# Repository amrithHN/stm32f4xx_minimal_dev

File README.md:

# Stm32f407 based board with barometer sensor

GPL license

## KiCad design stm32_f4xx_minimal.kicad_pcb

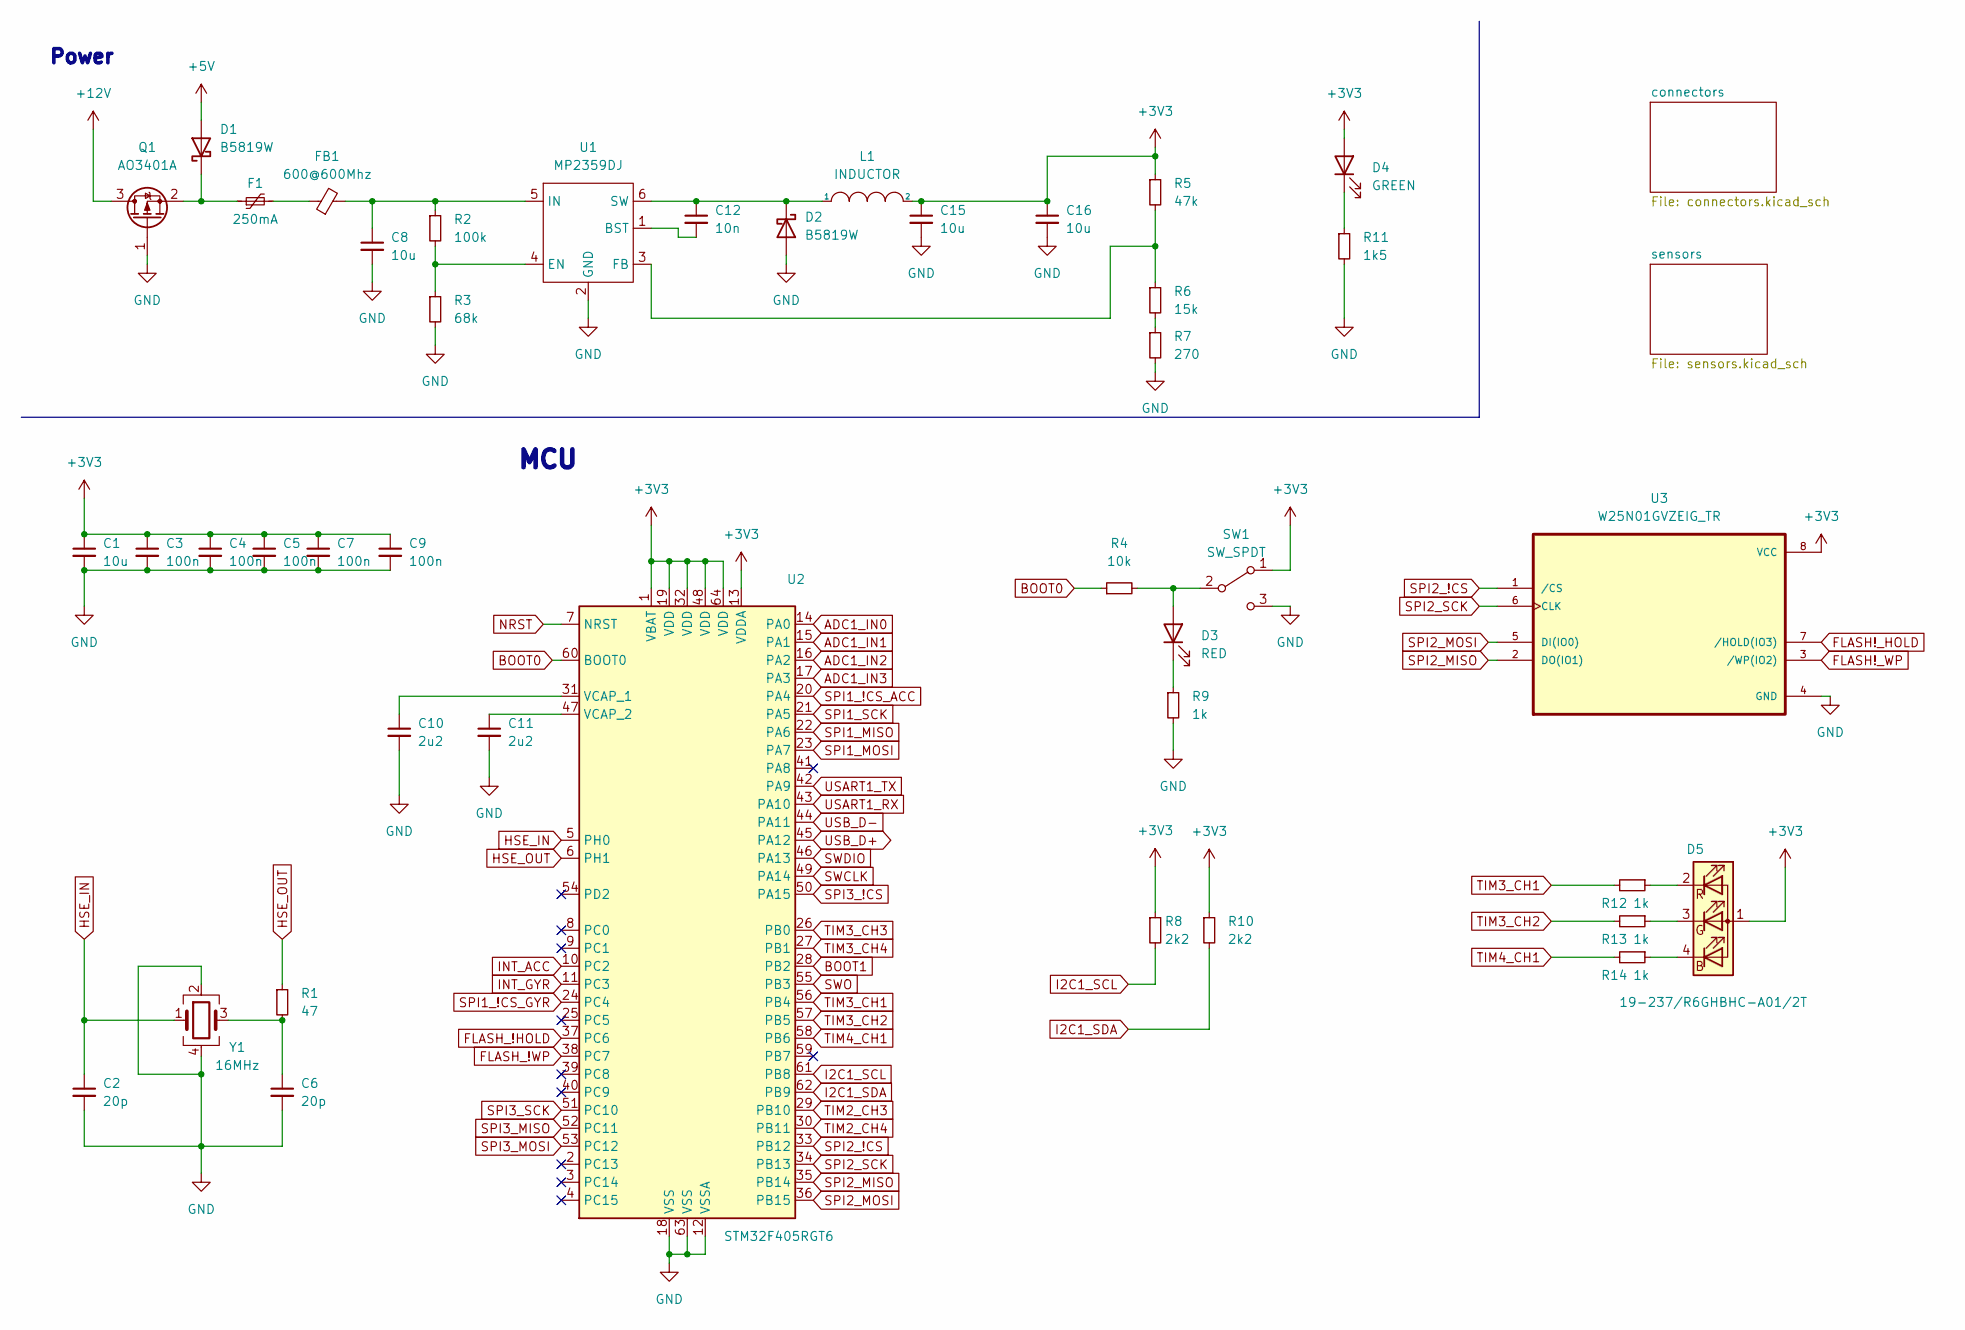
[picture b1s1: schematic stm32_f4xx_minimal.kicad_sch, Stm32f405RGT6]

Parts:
C1, C8: 10u; C_1206_3216Metric
C2, C6: 20p; C_0402_1005Metric
C3, C4, C5, C7, C9: 100n; C_0402_1005Metric
C10, C11: 2u2; C_0603_1608Metric
C12: 10n; C_0402_1005Metric
C15, C16: 10u; C_0603_1608Metric
D1, D2: B5819W; SOD3716X135N
D3: RED; LED_0603_1608Metric
D4: GREEN; LED_0603_1608Metric
D5: 19-237/R6GHBHC-A01/2T; 19-237-R6GHBHC-A01-2T
F1: 250mA; Fuse_1206_3216Metric
FB1: 600@600Mhz; L_0805_2012Metric
L1: INDUCTOR; L_Sunlord_MWSA0518_5.4x5.2mm
Q1: AO3401A; SOT-23
R1: 47; R_0402_1005Metric
R2: 100k; R_0603_1608Metric
R3: 68k; R_0603_1608Metric
R4: 10k; R_0603_1608Metric
R5: 47k; R_0603_1608Metric
R6: 15k; R_0603_1608Metric
R7: 270; R_0603_1608Metric
R8, R10: 2k2; R_0603_1608Metric
R9, R12, R13, R14: 1k; R_0603_1608Metric
R11: 1k5; R_0603_1608Metric
SW1: SW_SPDT; SW_SPDT_PCM12
U1: MP2359DJ; SOT-23-6
U2: STM32F405RGT6; LQFP-64_10x10mm_P0.5mm
U3: W25N01GVZEIG_TR; W25N01GVZEIG
Y1: 16MHz; Crystal_SMD_3225-4Pin_3.2x2.5mm

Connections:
+3V3: C1.1, C3.1, C4.1, C5.1, C7.1, C9.1, C15.1, C16.1, D4.2 (A), D5.1 (A), L1.2, R5.1, R8.1, R10.1, SW1.1 (A), U2.1 (VBAT), U2.13 (VDDA), U2.19 (VDD), U2.32 (VDD), U2.48 (VDD), U2.64 (VDD), U3.8 (VCC); also elsewhere on the board
+5V: D1.2 (A); also elsewhere on the board
+12V: Q1.3 (D); also elsewhere on the board
ADC1_IN0: U2.14 (PA0); also elsewhere on the board
ADC1_IN1: U2.15 (PA1); also elsewhere on the board
ADC1_IN2: U2.16 (PA2); also elsewhere on the board
ADC1_IN3: U2.17 (PA3); also elsewhere on the board
BOOT0: R4.1, U2.60 (BOOT0)
BOOT1: U2.28 (PB2)
FLASH!_HOLD: U3.7 (/HOLD(IO3))
FLASH!_WP: U3.3 (/WP(IO2))
FLASH_!HOLD: U2.37 (PC6)
FLASH_!WP: U2.38 (PC7)
GND: C1.2, C2.2, C3.2, C4.2, C5.2, C6.2, C7.2, C8.2, C9.2, C10.2, C11.2, C15.2, C16.2, D2.2 (A), Q1.1 (G), R3.2, R7.2, R9.2, R11.2, SW1.3 (C), U1.2 (GND), U2.12 (VSSA), U2.18 (VSS), U2.63 (VSS), U3.4 (GND), Y1.2, Y1.4; also elsewhere on the board
HSE_IN: C2.1, U2.5 (PH0), Y1.1
HSE_OUT: R1.1, U2.6 (PH1)
I2C1_SCL: R8.2, U2.61 (PB8); also elsewhere on the board
I2C1_SDA: R10.2, U2.62 (PB9); also elsewhere on the board
INT_ACC: U2.10 (PC2); also elsewhere on the board
INT_GYR: U2.11 (PC3); also elsewhere on the board
NRST: U2.7 (NRST); also elsewhere on the board
unnamed: C6.1, R1.2, Y1.3
unnamed: C8.1, FB1.2, R2.1, U1.5 (IN)
unnamed: C10.1, U2.31 (VCAP_1)
unnamed: C11.1, U2.47 (VCAP_2)
unnamed: C12.1, D2.1 (K), L1.1, U1.6 (SW)
unnamed: C12.2, U1.1 (BST)
unnamed: D1.1 (K), F1.1, Q1.2 (S)
unnamed: D3.1 (K), R9.1
unnamed: D3.2 (A), R4.2, SW1.2 (B)
unnamed: D4.1 (K), R11.1
unnamed: D5.2 (RK), R12.1
unnamed: D5.3 (GK), R13.1
unnamed: D5.4 (BK), R14.1
unnamed: F1.2, FB1.1
unnamed: R2.2, R3.1, U1.4 (EN)
unnamed: R5.2, R6.1, U1.3 (FB)
unnamed: R6.2, R7.1
SPI1_!CS_ACC: U2.20 (PA4); also elsewhere on the board
SPI1_!CS_GYR: U2.24 (PC4); also elsewhere on the board
SPI1_MISO: U2.22 (PA6); also elsewhere on the board
SPI1_MOSI: U2.23 (PA7); also elsewhere on the board
SPI1_SCK: U2.21 (PA5); also elsewhere on the board
SPI2_!CS: U2.33 (PB12), U3.1 (/CS)
SPI2_MISO: U2.35 (PB14), U3.2 (DO(IO1))
SPI2_MOSI: U2.36 (PB15), U3.5 (DI(IO0))
SPI2_SCK: U2.34 (PB13), U3.6 (CLK)
SPI3_!CS: U2.50 (PA15); also elsewhere on the board
SPI3_MISO: U2.52 (PC11); also elsewhere on the board
SPI3_MOSI: U2.53 (PC12); also elsewhere on the board
SPI3_SCK: U2.51 (PC10); also elsewhere on the board
SWCLK: U2.49 (PA14); also elsewhere on the board
SWDIO: U2.46 (PA13); also elsewhere on the board
SWO: U2.55 (PB3); also elsewhere on the board
TIM2_CH3: U2.29 (PB10); also elsewhere on the board
TIM2_CH4: U2.30 (PB11); also elsewhere on the board
TIM3_CH1: R12.2, U2.56 (PB4)
TIM3_CH2: R13.2, U2.57 (PB5)
TIM3_CH3: U2.26 (PB0); also elsewhere on the board
TIM3_CH4: U2.27 (PB1); also elsewhere on the board
TIM4_CH1: R14.2, U2.58 (PB6)
USART1_RX: U2.43 (PA10); also elsewhere on the board
USART1_TX: U2.42 (PA9); also elsewhere on the board
USB_D+: U2.45 (PA12); also elsewhere on the board
USB_D-: U2.44 (PA11); also elsewhere on the board

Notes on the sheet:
MCU
Power

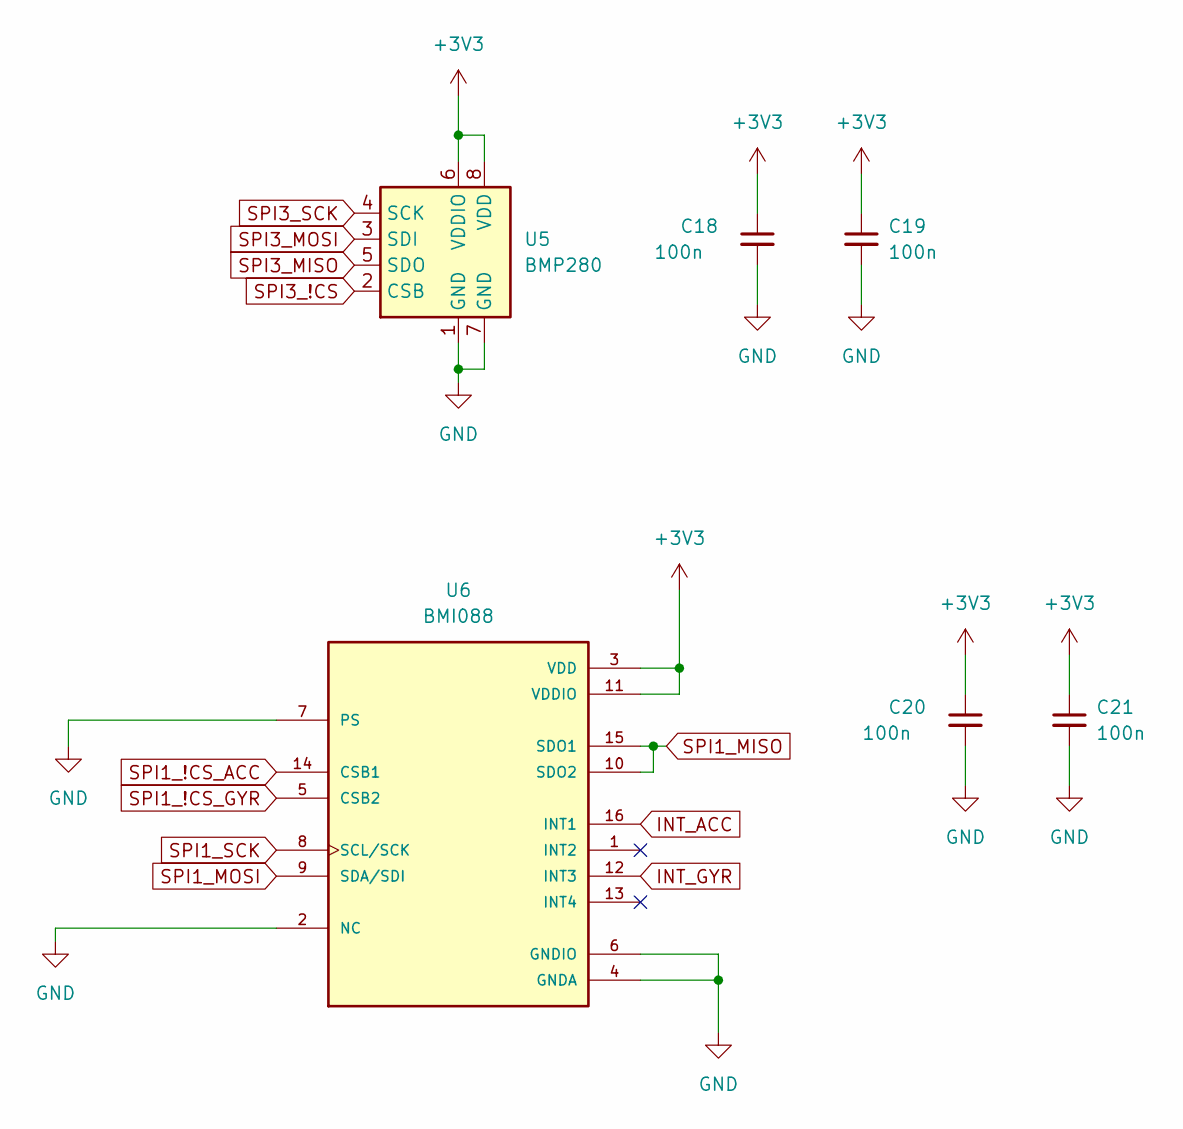
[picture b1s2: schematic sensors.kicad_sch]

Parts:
C18, C19, C20, C21: 100n; C_0402_1005Metric
U5: BMP280; Bosch_LGA-8_2x2.5mm_P0.65mm_ClockwisePinNumbering
U6: BMI088

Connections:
+3V3: C18.1, C19.1, C20.1, C21.1, U5.6 (VDDIO), U5.8 (VDD), U6.3 (VDD), U6.11 (VDDIO); also elsewhere on the board
GND: C18.2, C19.2, C20.2, C21.2, U5.1 (GND), U5.7 (GND), U6.2 (NC), U6.4 (GNDA), U6.6 (GNDIO), U6.7 (PS); also elsewhere on the board
INT_ACC: U6.16 (INT1); also elsewhere on the board
INT_GYR: U6.12 (INT3); also elsewhere on the board
SPI1_!CS_ACC: U6.14 (CSB1); also elsewhere on the board
SPI1_!CS_GYR: U6.5 (CSB2); also elsewhere on the board
SPI1_MISO: U6.10 (SDO2), U6.15 (SDO1); also elsewhere on the board
SPI1_MOSI: U6.9 (SDA/SDI); also elsewhere on the board
SPI1_SCK: U6.8 (SCL/SCK); also elsewhere on the board
SPI3_!CS: U5.2 (CSB); also elsewhere on the board
SPI3_MISO: U5.5 (SDO); also elsewhere on the board
SPI3_MOSI: U5.3 (SDI); also elsewhere on the board
SPI3_SCK: U5.4 (SCK); also elsewhere on the board

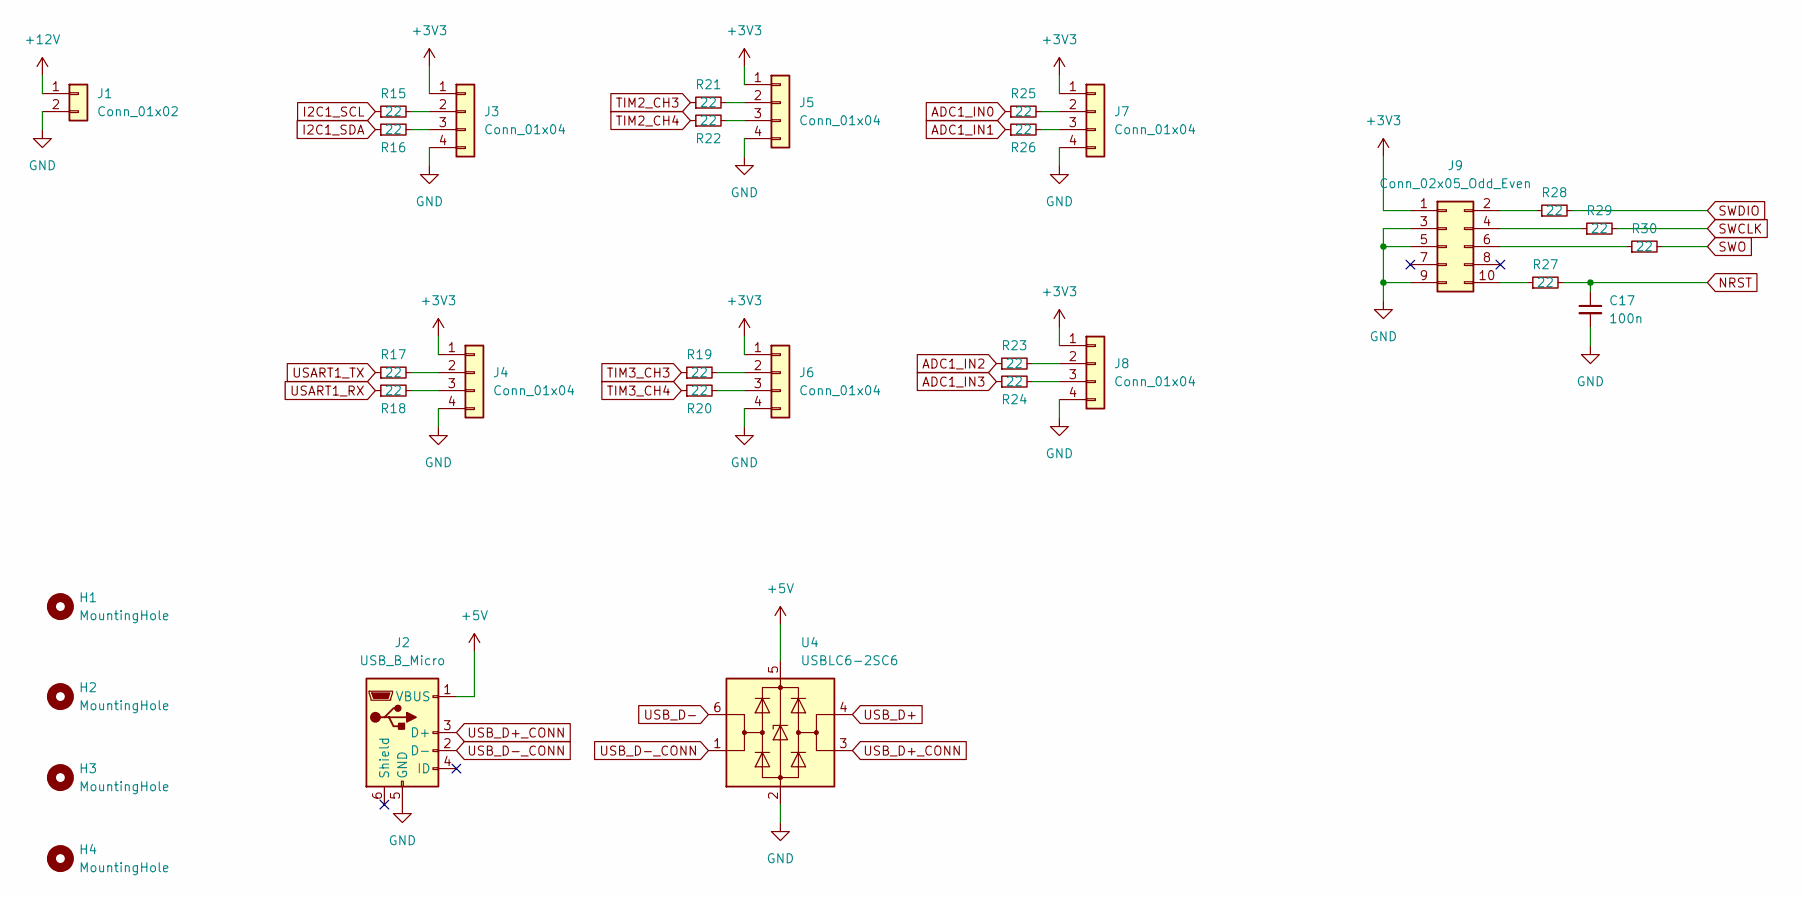
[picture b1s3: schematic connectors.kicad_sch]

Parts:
C17: 100n; C_0402_1005Metric
H1, H2, H3, H4: MountingHole; MountingHole_3.2mm_M3_Pad
J1: Conn_01x02; Molex_PicoBlade_53048-0210_1x02_P1.25mm_Horizontal
J2: USB_B_Micro; USB_Micro-B_Wuerth_629105150521
J3, J4, J5, J6, J7, J8: Conn_01x04; Molex_PicoBlade_53048-0410_1x04_P1.25mm_Horizontal
J9: Conn_02x05_Odd_Even; PinHeader_2x05_P1.27mm_Vertical_SMD
R15, R16, R17, R18, R19, R20, R21, R22, R23, R24, R25, R26, R27, R28, R29, R30: 22; R_0402_1005Metric
U4: USBLC6-2SC6; SOT-23-6

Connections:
+3V3: J3.1, J4.1, J5.1, J6.1, J7.1, J8.1, J9.1; also elsewhere on the board
+5V: J2.1 (VBUS), U4.5 (VBUS); also elsewhere on the board
+12V: J1.1; also elsewhere on the board
ADC1_IN0: R25.1; also elsewhere on the board
ADC1_IN1: R26.1; also elsewhere on the board
ADC1_IN2: R23.1; also elsewhere on the board
ADC1_IN3: R24.1; also elsewhere on the board
GND: C17.2, J1.2, J2.5 (GND), J3.4, J4.4, J5.4, J6.4, J7.4, J8.4, J9.3, J9.5, J9.9, U4.2 (GND); also elsewhere on the board
I2C1_SCL: R15.1; also elsewhere on the board
I2C1_SDA: R16.1; also elsewhere on the board
NRST: C17.1, R27.2; also elsewhere on the board
unnamed: J3.2, R15.2
unnamed: J3.3, R16.2
unnamed: J4.2, R17.2
unnamed: J4.3, R18.2
unnamed: J5.2, R21.2
unnamed: J5.3, R22.2
unnamed: J6.2, R19.2
unnamed: J6.3, R20.2
unnamed: J7.2, R25.2
unnamed: J7.3, R26.2
unnamed: J8.2, R23.2
unnamed: J8.3, R24.2
unnamed: J9.2, R28.1
unnamed: J9.4, R29.1
unnamed: J9.6, R30.1
unnamed: J9.10, R27.1
SWCLK: R29.2; also elsewhere on the board
SWDIO: R28.2; also elsewhere on the board
SWO: R30.2; also elsewhere on the board
TIM2_CH3: R21.1; also elsewhere on the board
TIM2_CH4: R22.1; also elsewhere on the board
TIM3_CH3: R19.1; also elsewhere on the board
TIM3_CH4: R20.1; also elsewhere on the board
USART1_RX: R18.1; also elsewhere on the board
USART1_TX: R17.1; also elsewhere on the board
USB_D+: U4.4 (I/O2); also elsewhere on the board
USB_D+_CONN: J2.3 (D+), U4.3 (I/O2)
USB_D-: U4.6 (I/O1); also elsewhere on the board
USB_D-_CONN: J2.2 (D-), U4.1 (I/O1)

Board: 4 copper layers, 79 parts (0 on the bottom side), 78 nets, no tracks yet.

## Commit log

2022-11-20 initial commit
    basic schematic done
2022-11-21 updated schematic
2022-11-29 updated and parts placement
    basic parts placement
2022-11-29 added license
2022-11-29 license
